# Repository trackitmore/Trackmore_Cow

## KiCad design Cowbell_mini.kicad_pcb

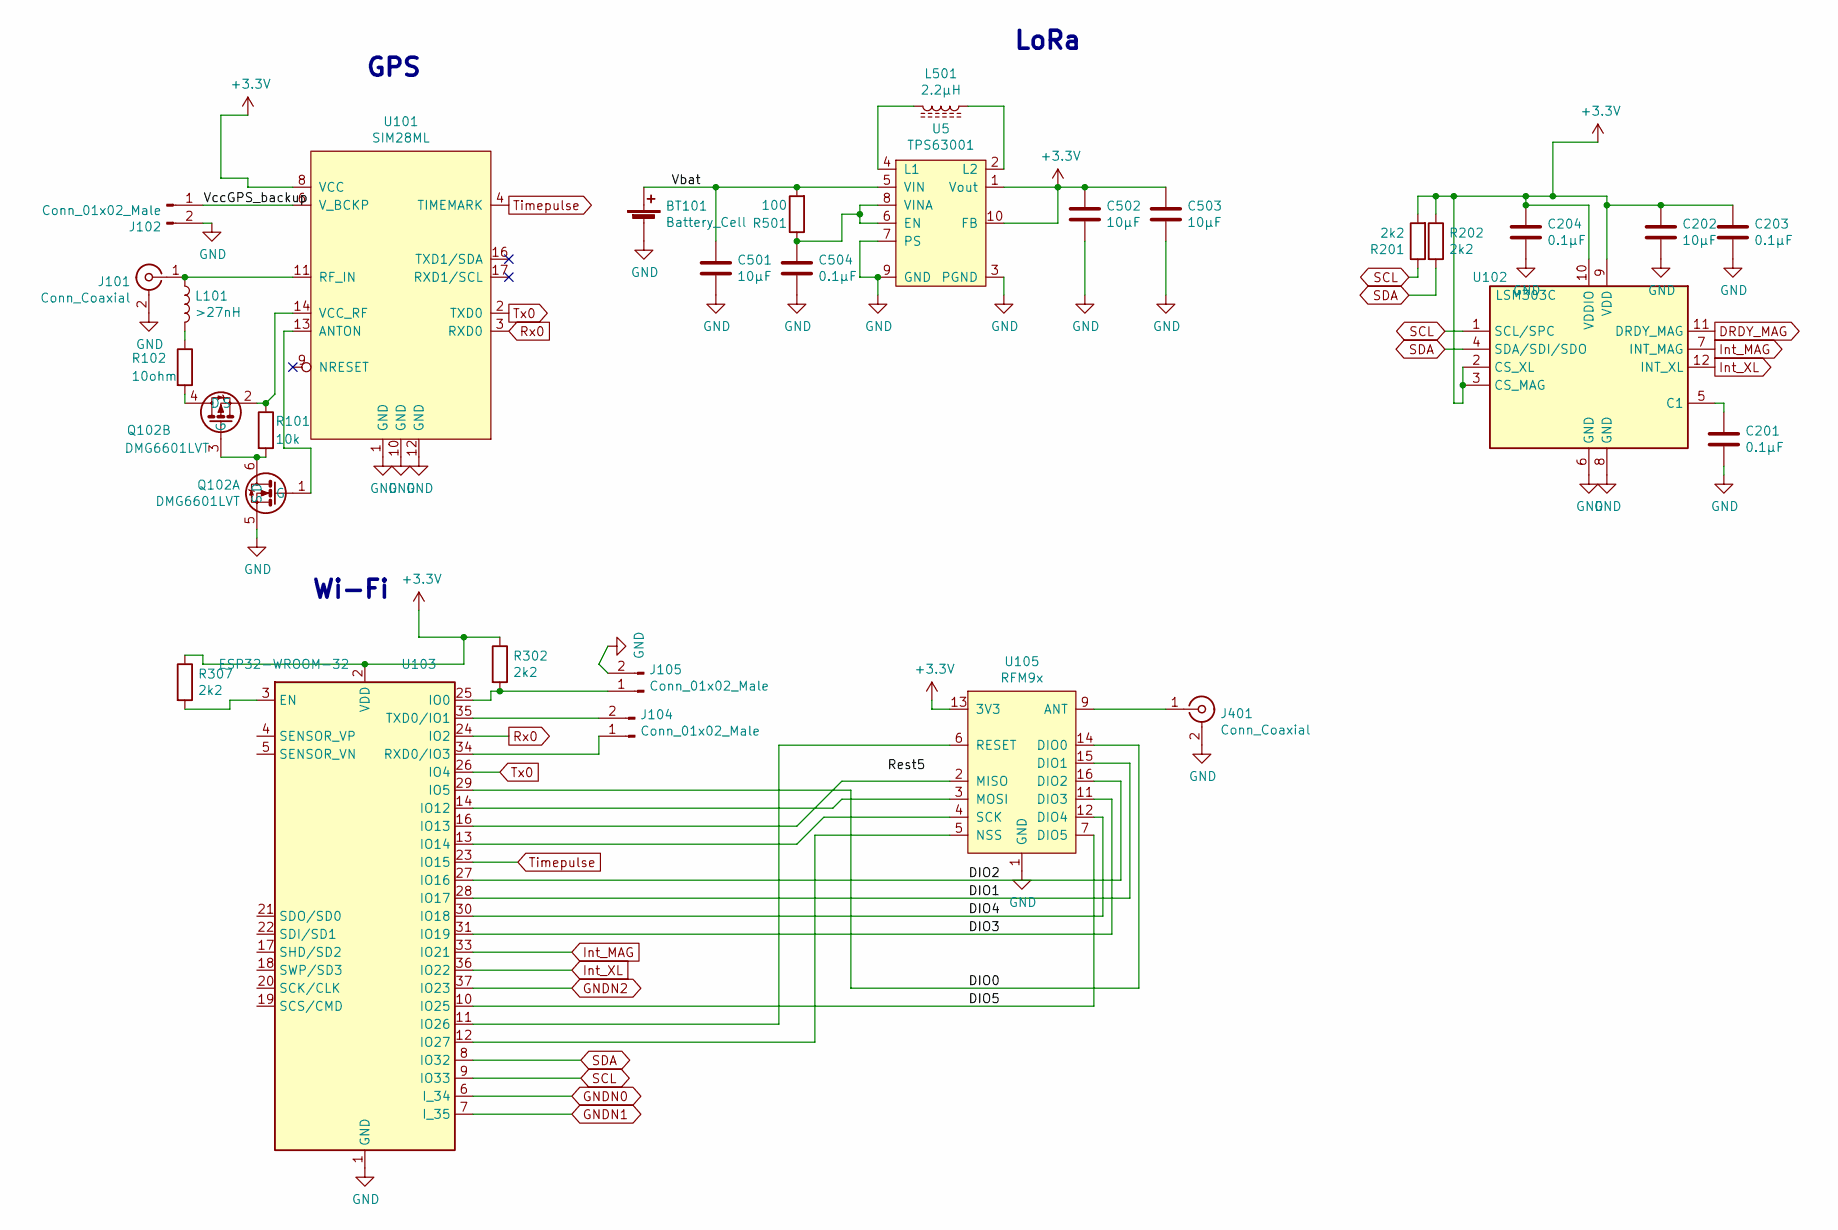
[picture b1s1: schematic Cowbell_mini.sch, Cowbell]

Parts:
BT101: Battery_Cell; batt_Connector
C201, C203, C204, C504: 0.1µF; C_0603_1608Metric
C202, C501, C502, C503: 10µF; C_0603_1608Metric
J101, J401: Conn_Coaxial; u.fl
J102, J104, J105: Conn_01x02_Male; Pin_Header_Straight_1x02_Pitch2.54mm
L101: >27nH; L_0402_1005Metric
L501: 2.2µH; NR3015
Q102: DMG6601LVT
R101: 10k; R_0603_1608Metric_Pad1.05x0.95mm_HandSolder
R102: 10ohm; R_0603_1608Metric_Pad1.05x0.95mm_HandSolder
R201, R202, R302, R307: 2k2; R_0603_1608Metric
R501: 100; R_0603_1608Metric_Pad1.05x0.95mm_HandSolder
U5: TPS63001; DRC0010J
U101: SIM28ML
U102: LSM303C; QFN-12_2x2_lsm303c
U103: ESP32-WROOM-32; ESP32-WROOM-32U
U105: RFM9x; RFM95

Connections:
+3V3: C202.1, C203.1, C204.1, C502.1, C503.1, R201.2, R202.1, R302.1, R307.1, U5.1 (Vout), U5.10 (FB), U101.8 (VCC), U102.2 (CS_XL), U102.3 (CS_MAG), U102.9 (VDD), U102.10 (VDDIO), U103.2 (VDD), U105.13 (3V3)
/DIO0: U103.29 (IO5), U105.14 (DIO0)
/DIO1: U103.28 (IO17), U105.15 (DIO1)
/DIO2: U103.27 (IO16), U105.16 (DIO2)
/DIO3: U103.31 (IO19), U105.11 (DIO3)
/DIO4: U103.30 (IO18), U105.12 (DIO4)
/DIO5: U103.10 (IO25), U105.7 (DIO5)
/Vbat: BT101.1 (+), C501.1, R501.2, U5.5 (VIN)
/VccGPS_backup: J102.1, U101.6 (V_BCKP)
DRDY_MAG: U102.11 (DRDY_MAG)
GND: BT101.2 (-), C201.2, C202.2, C203.2, C204.2, C501.2, C502.2, C503.2, C504.2, J101.2 (Ext), J102.2, J105.2, J401.2 (Ext), Q102.5 (S), U5.3 (PGND), U5.7 (PS), U5.9 (GND), U5.11 (PGND), U101.1 (GND), U101.10 (GND), U101.12 (GND), U102.6 (GND), U102.8 (GND), U103.1 (GND), U103.15 (GND), U103.38 (GND), U103.39 (GND), U105.1 (GND), U105.8 (GND), U105.10 (GND)
GNDN0: U103.6 (I_34)
GNDN1: U103.7 (I_35)
GNDN2: U103.37 (IO23)
Int_MAG: U102.7 (INT_MAG), U103.33 (IO21)
Int_XL: U102.12 (INT_XL), U103.36 (IO22)
unnamed: C201.1, U102.5 (C1)
unnamed: C504.1, R501.1, U5.6 (EN), U5.8 (VINA)
unnamed: J101.1 (In), L101.1, U101.11 (RF_IN)
unnamed: J104.1, U103.34 (RXD0/IO3)
unnamed: J104.2, U103.35 (TXD0/IO1)
unnamed: J105.1, R302.2, U103.25 (IO0)
unnamed: J401.1 (In), U105.9 (ANT)
unnamed: L101.2, R102.1
unnamed: L501.1, U5.2 (L2)
unnamed: L501.2, U5.4 (L1)
unnamed: Q102.1 (G), U101.13 (ANTON)
unnamed: Q102.2 (S), R101.1, U101.14 (VCC_RF)
unnamed: Q102.3 (G), Q102.6 (D), R101.2
unnamed: Q102.4 (D), R102.2
unnamed: R307.2, U103.3 (EN)
unnamed: U103.11 (IO26), U105.6 (RESET)
unnamed: U103.12 (IO27), U105.5 (NSS)
unnamed: U103.13 (IO14), U105.4 (SCK)
unnamed: U103.14 (IO12), U105.3 (MOSI)
unnamed: U103.16 (IO13), U105.2 (MISO)
Rx0: U101.3 (RXD0), U103.24 (IO2)
SCL: R201.1, U102.1 (SCL/SPC), U103.9 (IO33)
SDA: R202.2, U102.4 (SDA/SDI/SDO), U103.8 (IO32)
Timepulse: U101.4 (TIMEMARK), U103.23 (IO15)
Tx0: U101.2 (TXD0), U103.26 (IO4)

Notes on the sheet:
GPS
Wi-Fi
LoRa

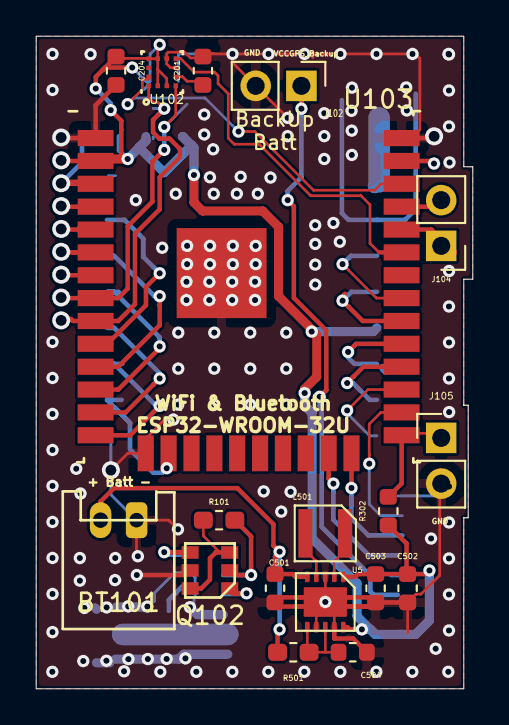
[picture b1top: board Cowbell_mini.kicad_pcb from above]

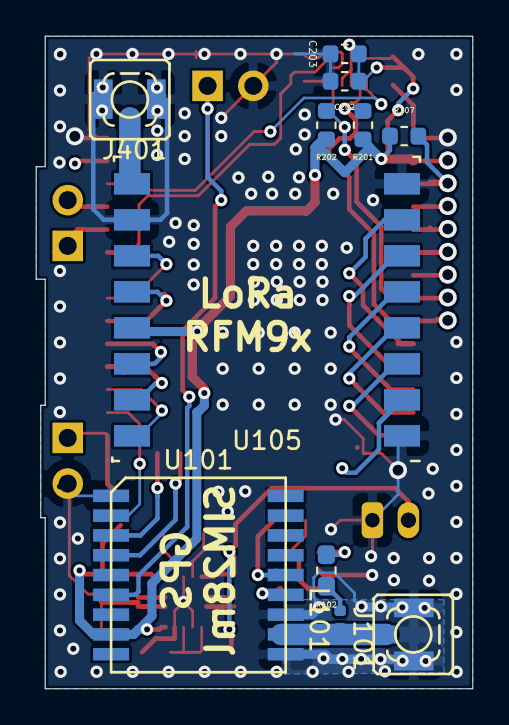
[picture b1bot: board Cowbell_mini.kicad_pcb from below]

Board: 2 copper layers, 24.2 x 36.2 mm, 29 parts (11 on the bottom side), 37 nets.

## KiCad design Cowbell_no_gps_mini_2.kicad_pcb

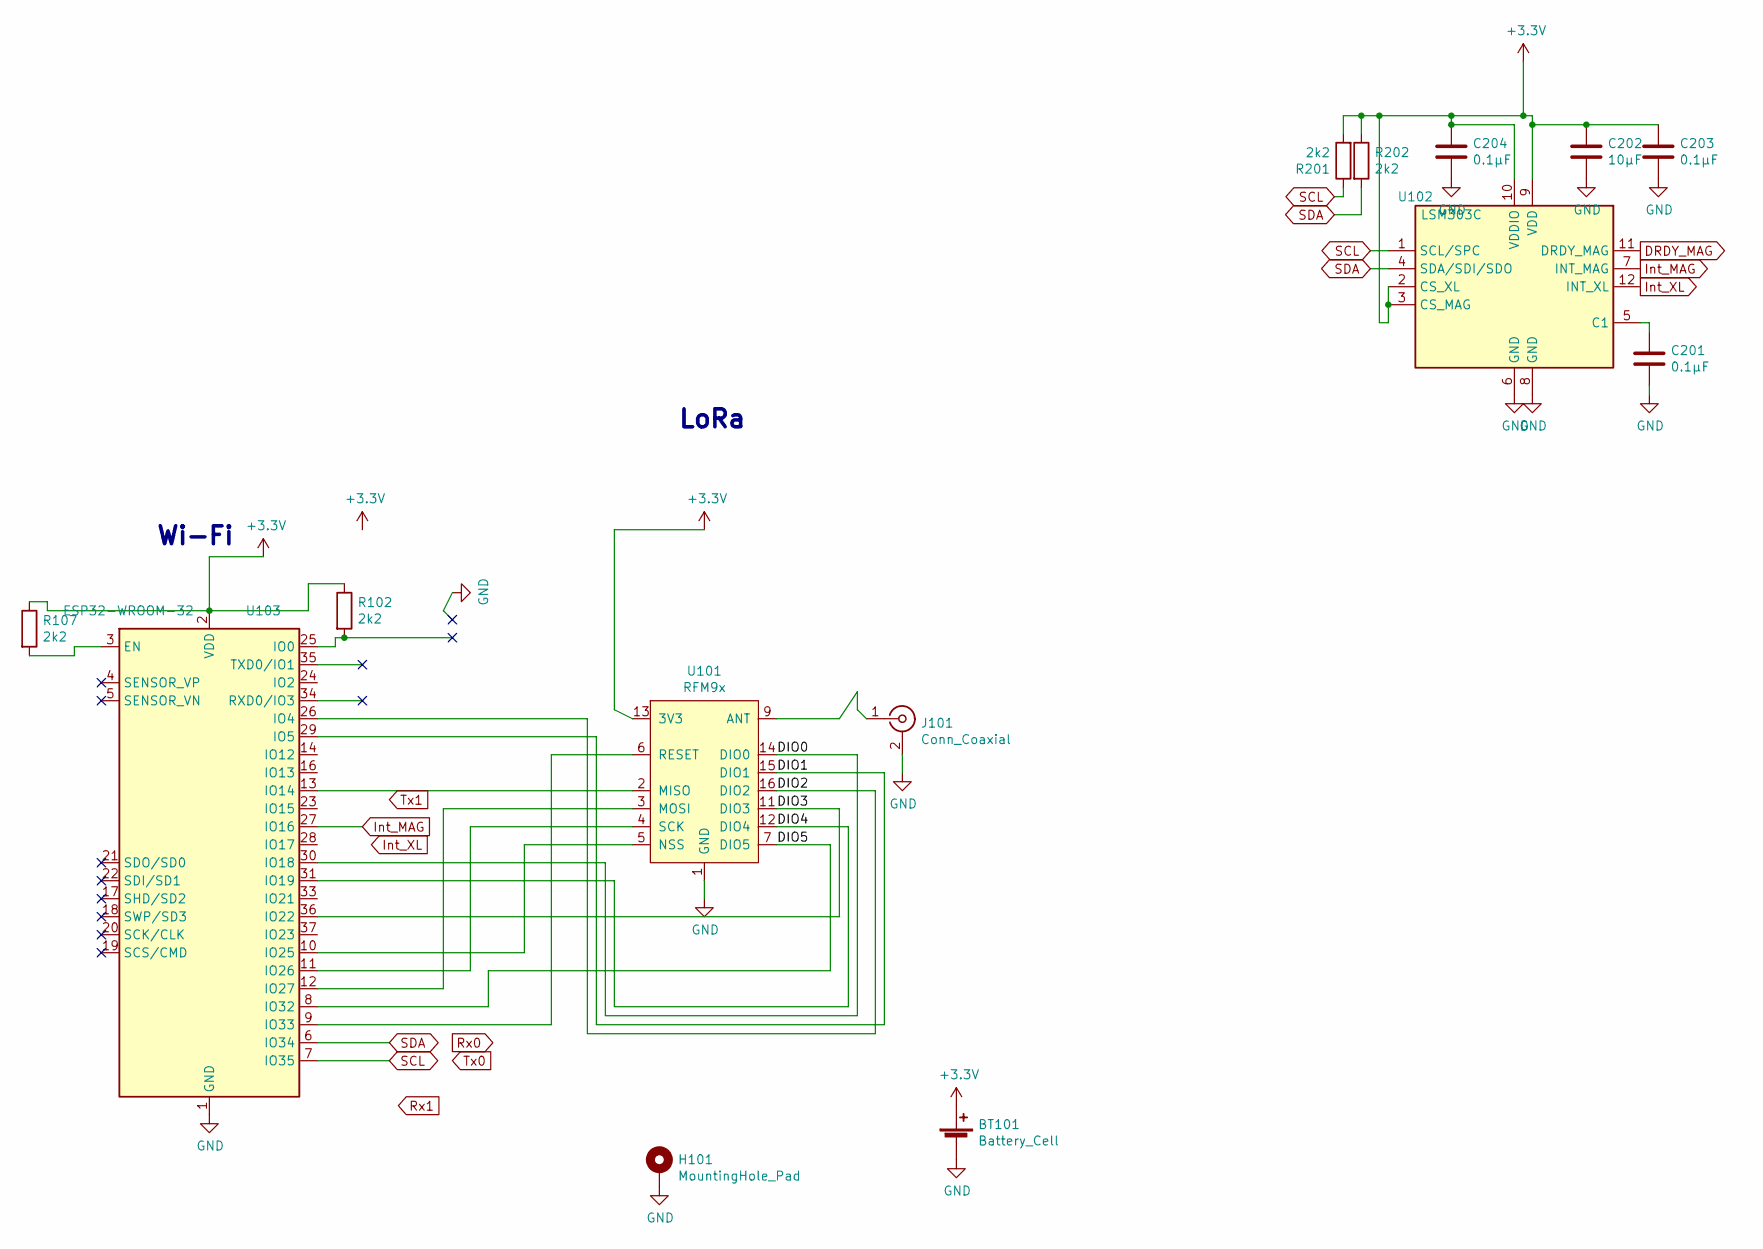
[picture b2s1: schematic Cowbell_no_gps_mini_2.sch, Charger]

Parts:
BT101: Battery_Cell; batt_Connector
C201, C203, C204: 0.1µF; C_0603_1608Metric
C202: 10µF; C_0603_1608Metric
H101: MountingHole_Pad; MountingHole_2.2mm_M2_Pad
J101: Conn_Coaxial; SMA_Molex_73251-1153_EdgeMount_Horizontal
R102, R107, R201, R202: 2k2; R_0603_1608Metric
U101: RFM9x; RFM95
U102: LSM303C; QFN-12_2x2_lsm303c
U103: ESP32-WROOM-32; SP32-WROOM-32U

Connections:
+3V3: BT101.1 (+), C202.1, C203.1, C204.1, R102.1, R107.1, R201.2, R202.1, U101.13 (3V3), U102.2 (CS_XL), U102.3 (CS_MAG), U102.9 (VDD), U102.10 (VDDIO), U103.2 (VDD)
/DIO0: U101.14 (DIO0), U103.30 (IO18)
/DIO1: U101.15 (DIO1), U103.29 (IO5)
/DIO2: U101.16 (DIO2), U103.26 (IO4)
/DIO3: U101.11 (DIO3), U103.36 (IO22)
/DIO4: U101.12 (DIO4), U103.31 (IO19)
/DIO5: U101.7 (DIO5), U103.8 (IO32)
DRDY_MAG: U102.11 (DRDY_MAG)
GND: BT101.2 (-), C201.2, C202.2, C203.2, C204.2, H101.1, J101.2 (Ext), U101.1 (GND), U101.8 (GND), U101.10 (GND), U102.6 (GND), U102.8 (GND), U103.1 (GND), U103.15 (GND), U103.38 (GND), U103.39 (GND)
Int_MAG: U102.7 (INT_MAG), U103.27 (IO16)
Int_XL: U102.12 (INT_XL)
unnamed: C201.1, U102.5 (C1)
unnamed: J101.1 (In), U101.9 (ANT)
unnamed: R102.2, U103.25 (IO0)
unnamed: R107.2, U103.3 (EN)
unnamed: U101.2 (MISO), U103.13 (IO14)
unnamed: U101.3 (MOSI), U103.12 (IO27)
unnamed: U101.4 (SCK), U103.11 (IO26)
unnamed: U101.5 (NSS), U103.10 (IO25)
unnamed: U101.6 (RESET), U103.9 (IO33)
SCL: R201.1, U102.1 (SCL/SPC), U103.7 (IO35)
SDA: R202.2, U102.4 (SDA/SDI/SDO), U103.6 (IO34)

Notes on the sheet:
Wi-Fi
LoRa

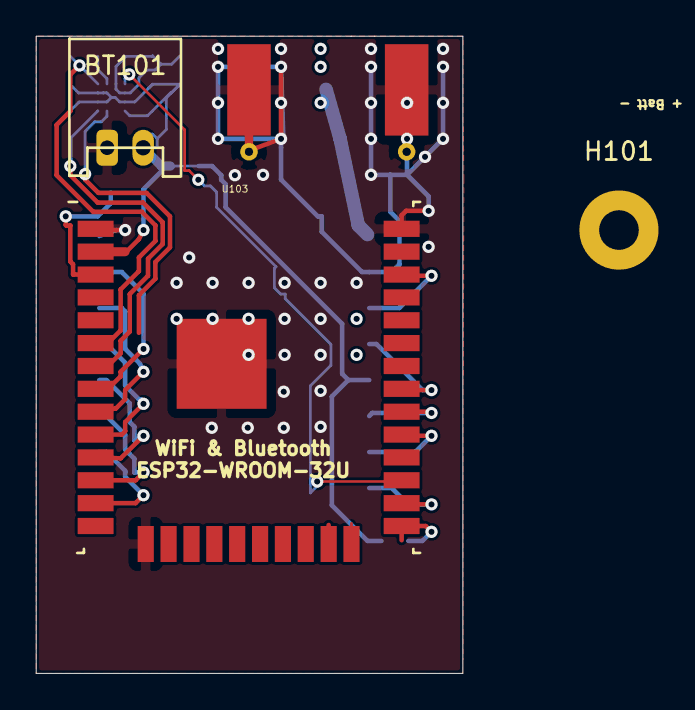
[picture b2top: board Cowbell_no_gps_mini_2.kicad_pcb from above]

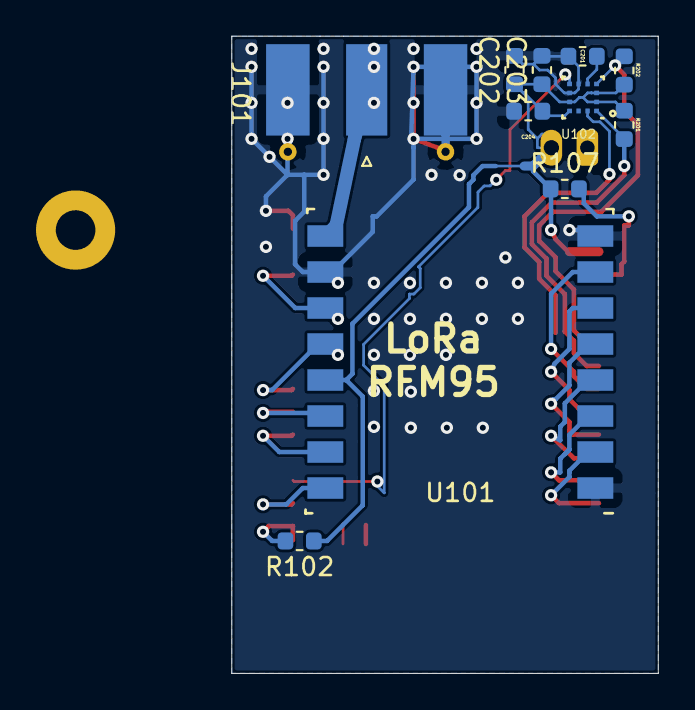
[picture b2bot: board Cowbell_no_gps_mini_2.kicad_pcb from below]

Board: 2 copper layers, 23.7 x 35.4 mm, 14 parts (11 on the bottom side), 20 nets.

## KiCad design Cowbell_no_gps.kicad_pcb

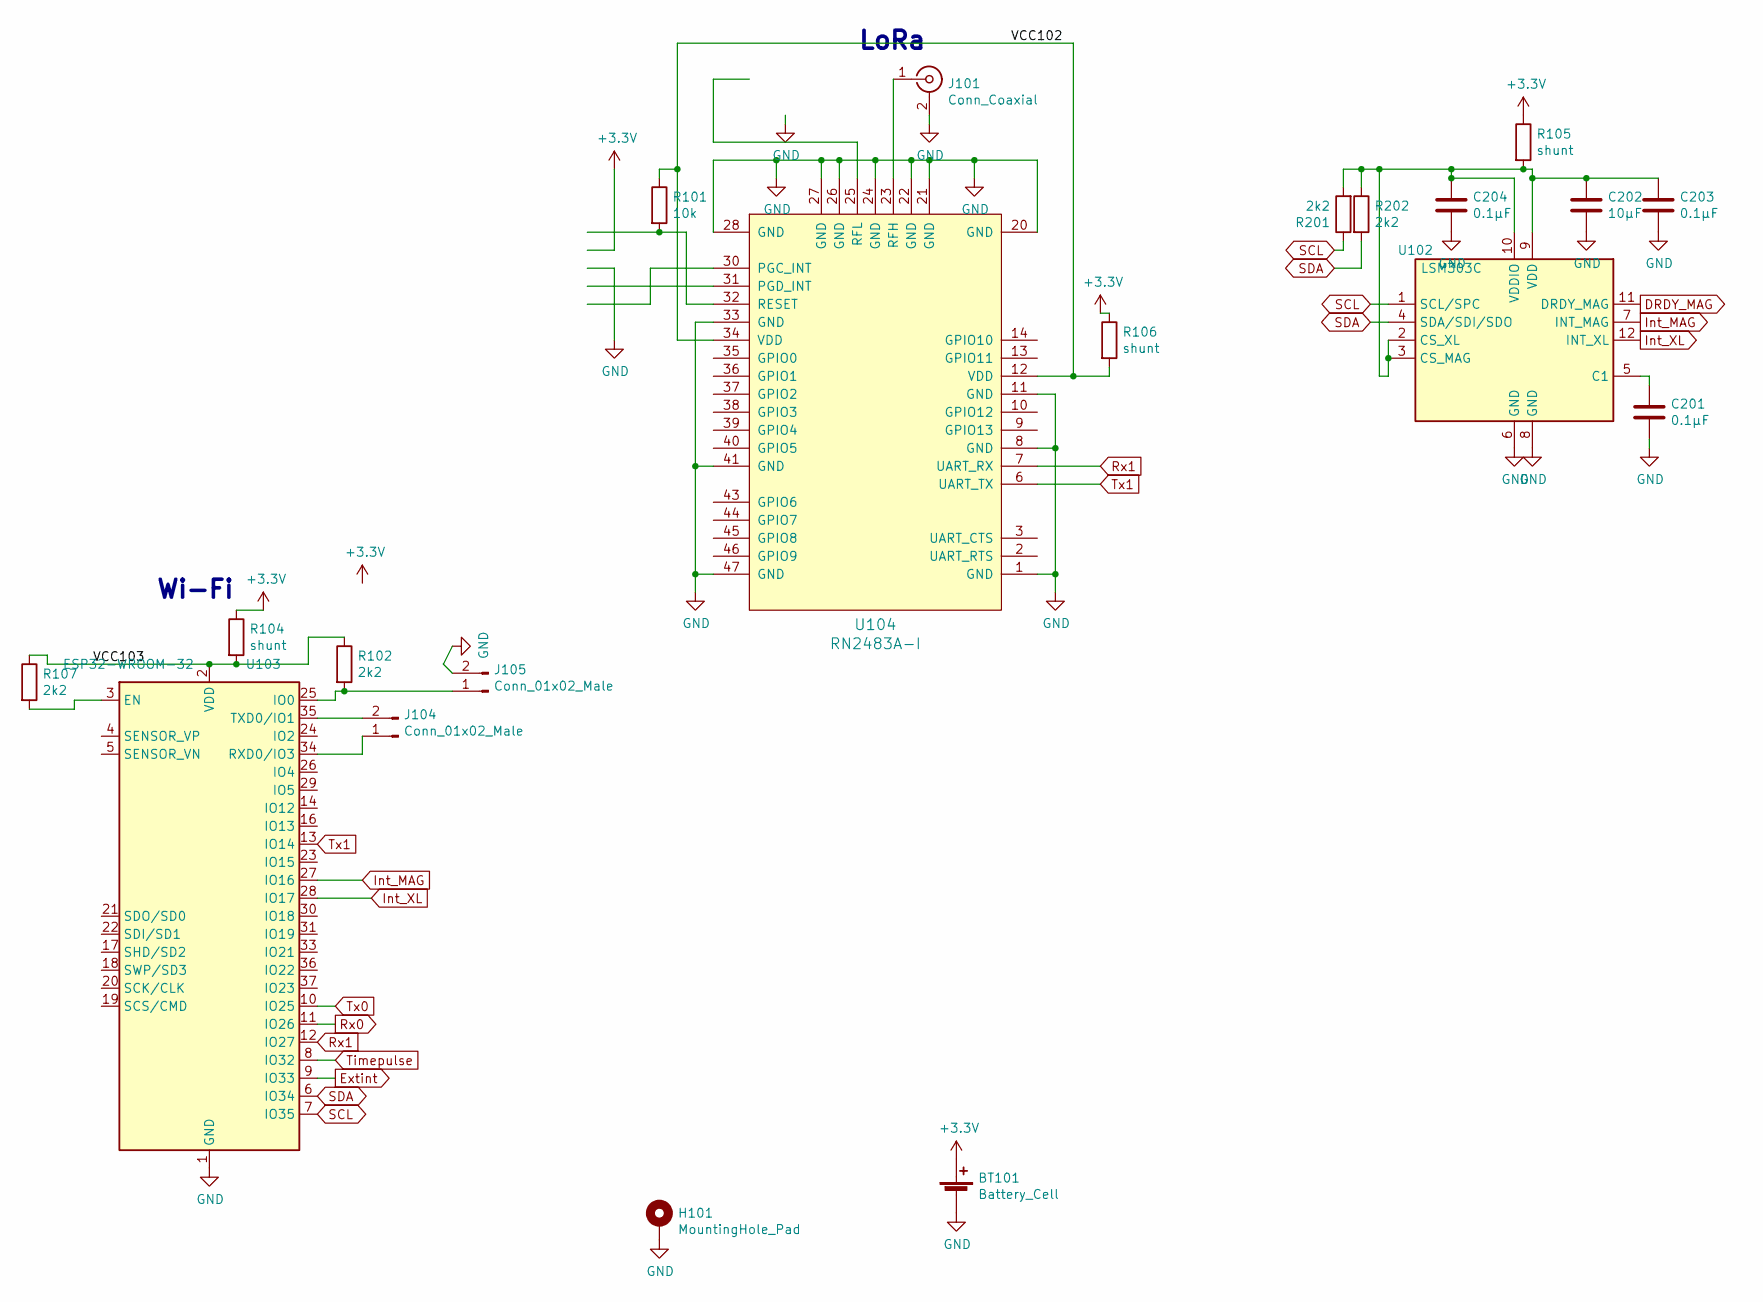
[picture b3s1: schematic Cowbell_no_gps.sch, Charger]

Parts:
BT101: Battery_Cell; batt_Connector
C201, C203, C204: 0.1µF; C_0603
C202: 10µF; C_0603_HandSoldering
H101: MountingHole_Pad; MountingHole_2.2mm_M2_Pad
J101: Conn_Coaxial; Molex_SMA_Jack_Edge_Mount
J104, J105: Conn_01x02_Male; Pin_Header_Straight_1x02_Pitch2.54mm
R101: 10k; R_0603_HandSoldering
R102, R107, R201, R202: 2k2; R_0603
R104, R105, R106: shunt; R_0603
U102: LSM303C; QFN-12_2x2_lsm303c
U103: ESP32-WROOM-32; SP32-WROOM-32U
U104: RN2483A-I; RN2483; Mouser_PN 579-RN2483A-I/RM104

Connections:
+3V3: BT101.1 (+), R104.1, R105.1, R106.1
/VCC102: R101.1, R106.2, U104.12 (VDD), U104.34 (VDD)
/VCC103: R102.1, R104.2, R107.1, U103.2 (VDD)
DRDY_MAG: U102.11 (DRDY_MAG)
Extint: U103.9 (IO33)
GND: BT101.2 (-), C201.2, C202.2, C203.2, C204.2, H101.1, J101.2 (Ext), J105.2, U102.6 (GND), U102.8 (GND), U103.1 (GND), U103.15 (GND), U103.38 (GND), U103.39 (GND), U104.1 (GND), U104.8 (GND), U104.11 (GND), U104.20 (GND), U104.21 (GND), U104.22 (GND), U104.24 (GND), U104.26 (GND), U104.27 (GND), U104.28 (GND), U104.33 (GND), U104.41 (GND), U104.47 (GND)
Int_MAG: U102.7 (INT_MAG), U103.27 (IO16)
Int_XL: U102.12 (INT_XL), U103.28 (IO17)
unnamed: C201.1, U102.5 (C1)
unnamed: C202.1, C203.1, C204.1, R105.2, R201.2, R202.1, U102.2 (CS_XL), U102.3 (CS_MAG), U102.9 (VDD), U102.10 (VDDIO)
unnamed: J101.1 (In), U104.23 (RFH)
unnamed: J104.1, U103.34 (RXD0/IO3)
unnamed: J104.2, U103.35 (TXD0/IO1)
unnamed: J105.1, R102.2, U103.25 (IO0)
unnamed: R101.2, U104.32 (RESET)
unnamed: R107.2, U103.3 (EN)
Rx0: U103.11 (IO26)
Rx1: U103.12 (IO27), U104.7 (UART_RX)
SCL: R201.1, U102.1 (SCL/SPC), U103.7 (IO35)
SDA: R202.2, U102.4 (SDA/SDI/SDO), U103.6 (IO34)
Timepulse: U103.8 (IO32)
Tx0: U103.10 (IO25)
Tx1: U103.13 (IO14), U104.6 (UART_TX)

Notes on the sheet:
Wi-Fi
LoRa

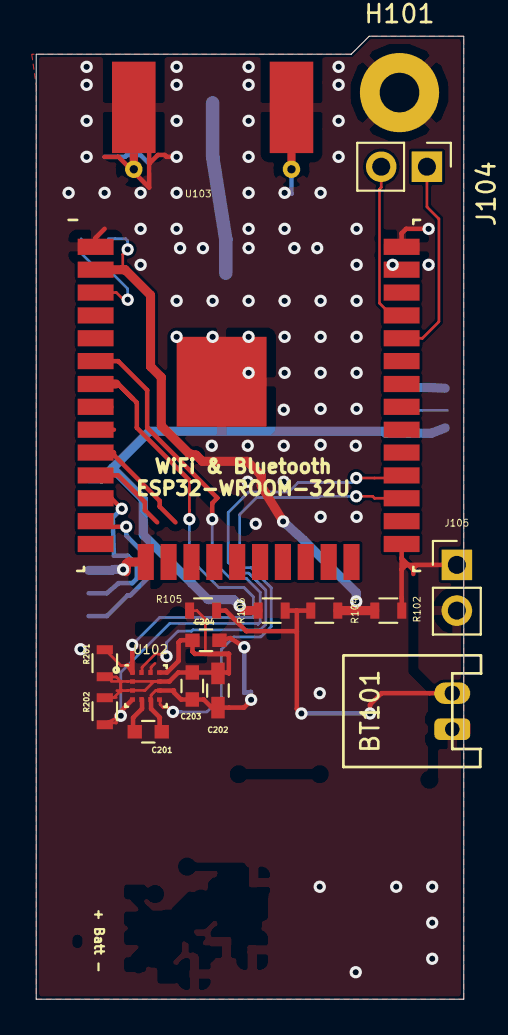
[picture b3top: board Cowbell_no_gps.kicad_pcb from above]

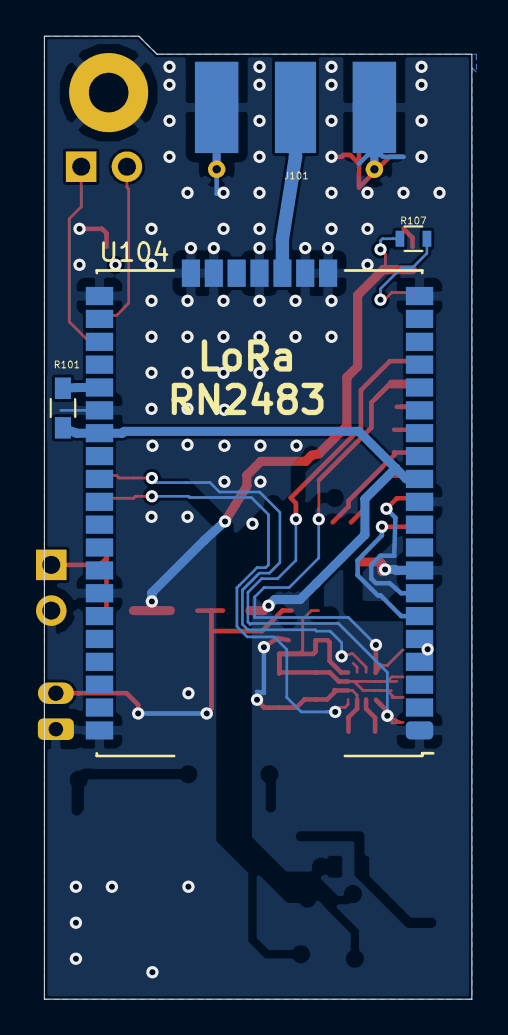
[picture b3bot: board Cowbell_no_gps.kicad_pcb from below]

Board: 2 copper layers, 23.7 x 53.5 mm, 20 parts (4 on the bottom side), 18 nets.

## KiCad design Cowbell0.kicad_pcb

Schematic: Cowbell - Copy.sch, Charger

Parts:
C1: 1nF; C_0603_HandSoldering
C2: 330pF; C_0603_HandSoldering
C3: C; C_0603_HandSoldering
C4: 0.1F; CP_Radial_D13.0mm_P5.00mm
C201, C203, C204: 0.1µF; C_0603
C202: 10µF; C_0603_HandSoldering
J1: Conn_Coaxial; u.fl
J10: V_BCKP; Pin_d0.9mm_L10.0mm_W2.4mm_FlatFork
J11: GND; Pin_d0.9mm_L10.0mm_W2.4mm_FlatFork
J101, J102: Conn_Coaxial; Molex_SMA_Jack_Edge_Mount
J103: Conn_01x06_Male; Pin_Header_Straight_1x06_Pitch2.54mm
J104, J105: Conn_01x02_Male; Pin_Header_Straight_1x02_Pitch2.54mm
L1: L_Core_Ferrite_Coupled; WE-EHPI 6x6
R1: DNC; R_0603_HandSoldering
R101: 10k; R_0603_HandSoldering
R201, R202: 2k2; R_0603
TP1, TP2, TP3, TP4, TP5, TP6: TestPoint; Pin_d0.9mm_L10.0mm_W2.4mm_FlatFork
TP_Vaux1: TestPoint; Pin_d0.9mm_L10.0mm_W2.4mm_FlatFork
TP_Vstor1: TestPoint; Pin_d0.9mm_L10.0mm_W2.4mm_FlatFork
U1: LTC3108; LTC3108_SSOP-16
U101: NEO-M8
U102: LSM303C; QFN-12_2x2_lsm303c
U103: ESP32-WROOM-32; SP32-WROOM-32U
U104: RN2483A-I; RN2483; Mouser_PN 579-RN2483A-I/RM104

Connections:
DRDY_MAG: U102.11 (DRDY_MAG)
Extint: U101.4 (EXTINT), U103.9 (IO33)
GND: C3.2, C4.2, C201.2, C202.2, C203.2, C204.2, J1.2 (Ext), J11.1, J101.2 (Ext), J102.2 (Ext), J103.3, J105.2, L1.4, U1.1, U1.8, U1.9, U1.10, U1.16, U101.10 (GND), U101.12 (GND), U101.13 (GND), U101.24 (GND), U102.6 (GND), U102.8 (GND), U103.1 (GND), U103.15 (GND), U103.38 (GND), U103.39 (GND), U104.1 (GND), U104.8 (GND), U104.11 (GND), U104.20 (GND), U104.21 (GND), U104.22 (GND), U104.24 (GND), U104.26 (GND), U104.27 (GND), U104.28 (GND), U104.33 (GND), U104.41 (GND), U104.47 (GND)
Int_MAG: U102.7 (INT_MAG)
Int_XL: U102.12 (INT_XL)
unnamed: C1.1, U1.13
unnamed: C1.2, C2.2, L1.3
unnamed: C2.1, U1.14
unnamed: C3.1, TP_Vaux1.1, U1.2, U1.11
unnamed: C4.1, TP_Vstor1.1, U1.3
unnamed: C201.1, U102.5 (C1)
unnamed: J1.1 (In), U101.11 (RF_IN)
unnamed: J10.1, U101.22 (V_BCKP)
unnamed: J101.1 (In), U104.23 (RFH)
unnamed: J102.1 (In), U104.25 (RFL)
unnamed: J103.1, R101.2, U104.32 (RESET)
unnamed: J103.4, U104.31 (PGD_INT)
unnamed: J103.5, U104.30 (PGC_INT)
unnamed: L1.1, TP1.1
unnamed: L1.2, U1.15
unnamed: R1.1, U101.9 (VCC_RF)
unnamed: R1.2, U101.8 (RESET_N)
unnamed: TP2.1, U1.5
unnamed: TP3.1, U1.7
unnamed: TP4.1, U1.6
unnamed: TP5.1, U1.12
unnamed: TP6.1, U1.4
unnamed: J105.1, U103.25 (IO0)
unnamed: J104.1, U103.34 (RXD0/IO3)
unnamed: J104.2, U103.35 (TXD0/IO1)
Rx0: U101.21 (RXD), U103.11 (IO26)
Rx1: U103.12 (IO27), U104.7 (UART_RX)
SCL: R201.1, U102.1 (SCL/SPC), U103.7 (IO35)
SDA: R202.2, U102.4 (SDA/SDI/SDO), U103.6 (IO34)
Timepulse: U101.3 (TIMEPULS), U103.8 (IO32)
Tx0: U101.20 (TXD), U103.10 (IO25)
Tx1: U103.13 (IO14), U104.6 (UART_TX)

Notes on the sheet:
GPS
Wi-Fi
LoRa

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
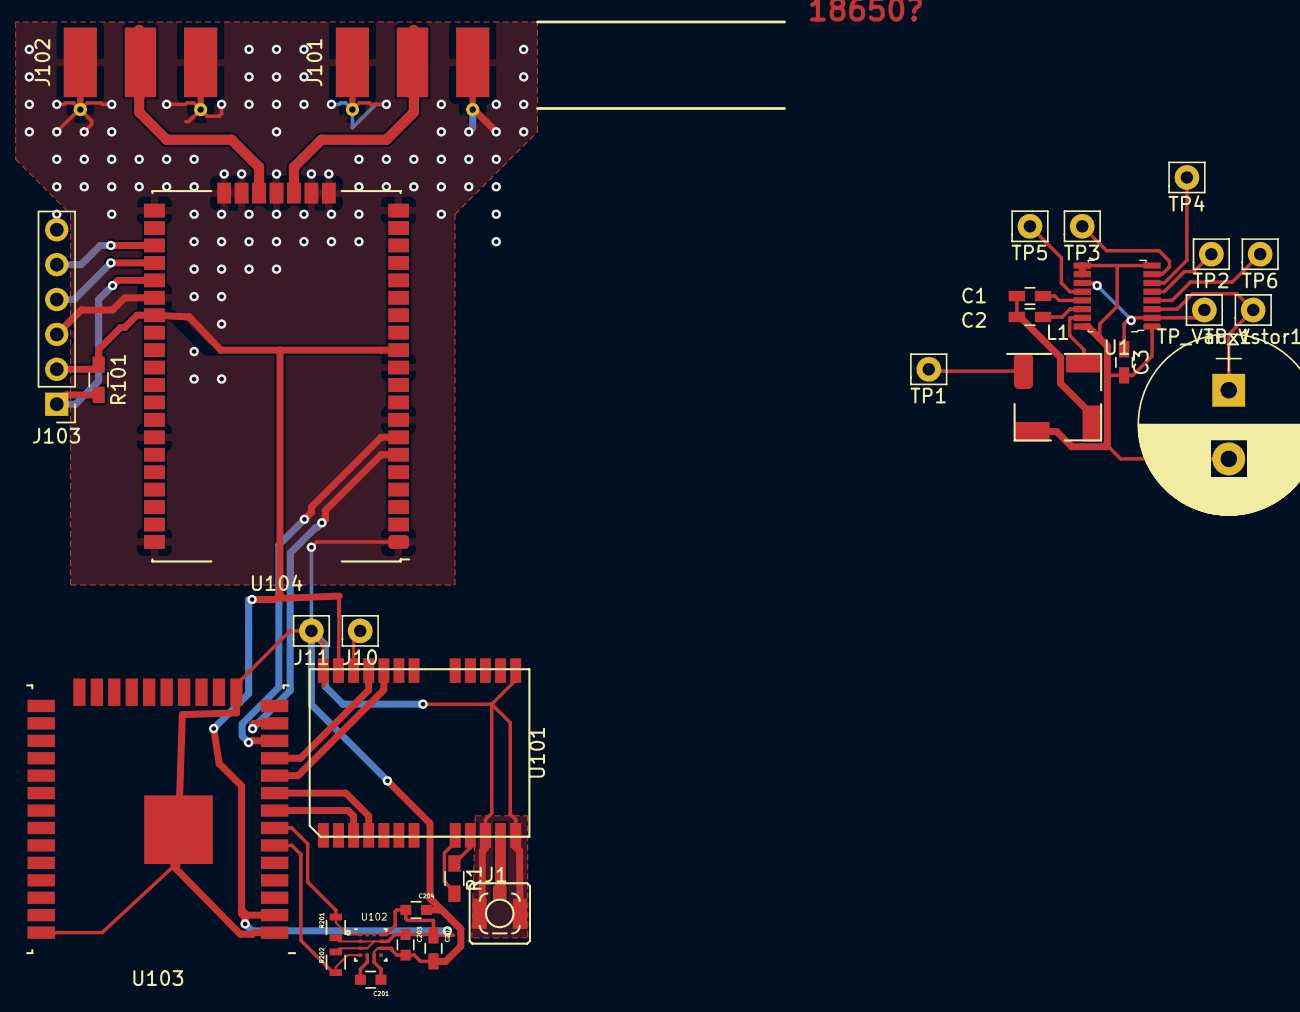
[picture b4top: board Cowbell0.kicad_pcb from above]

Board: 2 copper layers, 32 parts (0 on the bottom side), 32 nets.

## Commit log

2019-03-12 Finished design
2019-04-02 Revert "Delete Emborg.bck"
    This reverts commit 09d27a02d29fe968c1b7a81d1ac8e51f44b27ffa.
2019-04-02 Revert "Delete Emborg.dcm"
    This reverts commit c4a0c2c87ce3134f79510e9a5a0e6fc7b62b94bc.
2019-04-02 Revert "Delete Emborg.lib"
    This reverts commit cf9496bd58ba884746e156cb7f657ddb5a494be7.
2019-04-02 Revert "Delete sym-lib-table"
    This reverts commit 0304bca046c8f614dbed9e12e921aacf97358f74.
2019-04-02 Revert "Delete thinkerbell.kicad_pcb-bak"
    This reverts commit 65bb71eede209ff8c9db95584b85d2a653b0d64a.
2019-04-02 Revert "Delete thinkerbell.pro"
    This reverts commit 58df75db17a912b9343e4aff8fe34464ce08963a.
2019-04-02 Revert "Delete Cowbell1.kicad_pcb"
    This reverts commit d80b693f933305171241f23dd8f8959974bb5168.
2019-04-02 Revert "Delete Cowbell0.kicad_pcb"
    This reverts commit 252e33d99e0bc0e285b6e3a8f17d518fcc3dd87e.
2019-04-02 Revert "Delete Cowbell.sch"
    This reverts commit 978fadb779a8fa3cc5b9792794aa4cbf9cfdb8ff.
2019-04-02 Revert "Delete Cowbell.xml"
    This reverts commit 881aa0ef93652d590a35256fd297fa05b056862a.
2019-04-02 Revert "Delete Cowbell.pro"
    This reverts commit 091eba08f6241ed96e29c814f36a258aab0e2ca5.
2019-04-02 Revert "Delete Cowbell.net"
    This reverts commit 7cafb855b5cd9209ead3aa4c814db5f94e171ee6.
2019-04-02 Revert "Delete Cowbell - Copy.sch"
    This reverts commit ae1c11a69f8279535f7880325fb270926ae6e74f.
2019-04-02 Revert "Delete .gitattributes"
    This reverts commit 4acfe99408becdc238a615270ff10b1e2c5de4c9.
2019-04-02 Revert "Delete LTC3108_SSOP-16.kicad_mod"
    This reverts commit f564a00daeaa7909a267ca2040881fb35d2d5901.
2019-04-02 Revert "Delete NEO-M8.kicad_mod"
    This reverts commit 1ef6422d8f3c24d0bca9058cdd3533081b6ed742.
2019-04-02 Revert "Delete QFN-12_2x2_lsm303c.kicad_mod"
    This reverts commit 21fc2b2070f548b9e88a3c2e228f056f9d769ac0.
2019-04-02 Revert "Delete QFP-80_17.78x26.67_Pitch1.27mm.kicad_mod"
    This reverts commit 5e69e16ba0a7954603f7a7df822ec4fd45762fe7.
2019-04-02 Revert "Delete RN2483.kicad_mod"
    This reverts commit e23ea6ab3ff4c29680038cb41fe7873a4a4a5c81.
2019-04-02 Revert "Delete SP32-WROOM-32U.kicad_mod"
    This reverts commit 5fa6db17635eadc840dfb2fc761eeff62a0f5e57.
2019-04-02 Revert "Delete SSOP-16-LTC3108.kicad_mod"
    This reverts commit 1ba041bbb633a4fccae1273e11786fdac62c0148.
2019-04-02 Revert "Delete batt_Connector.kicad_mod"
    This reverts commit 9847d93e790d4d2d9b095128e2b6511a8e429725.
2019-04-02 Revert "Delete WE-EHPI 6x6.kicad_mod"
    This reverts commit 5fb4d74c714d4724239fdc0bf541602c3e96ddf4.
2019-04-02 Revert "Delete u.fl.kicad_mod"
    This reverts commit 5432f16fb51e91493d83f1e084b6664b42315e9d.
2019-04-02 Revert "Delete Cowbell-cache.lib"
    This reverts commit deac368cf7cbae8f2a3d845c4ad8eac762145e6c.
2019-04-02 Revert "Delete Cowbell-rescue.dcm"
    This reverts commit 3877b9671cf0eeddc5ad82af6c877a2a42698372.
2019-04-02 Revert "Delete Cowbell-rescue.lib"
    This reverts commit 5e4fc595a82f6b163571de27dac84ba1a4aeee0b.
2019-04-02 Revert "Delete Cowbell.bak"
    This reverts commit 83bee5dd43be2db377b36096ba5a354214a55166.
2019-04-02 Revert "Delete Cowbell.kicad_pcb"
    This reverts commit 747ba4d31c338c22f969143d4c642bb9dc160634.
2019-04-02 Revert "Delete Cowbell.kicad_pcb-bak"
    This reverts commit a0f5cc8e1a52d7afc8a1a5b4756ecd4a47175799.
2019-04-05 Removed unnissray files
2019-04-05 Added code
2019-04-11 Add files via upload
    skifte til sim28
2019-04-26 Upload
2019-04-26 Revert "Added code"
    This reverts commit 917a6e6e95a4ee82794b217ccadd158d93d931af.
2019-04-26 Revert "Removed unnissray files"
    This reverts commit eb4dde10ade02bed4aa6936b6fc7d44ad99826a2.
2019-04-26 Revert "Upload"
    This reverts commit f814fb6d94db8a858d7b366ca888cf0d9b009713.
2019-05-04 Updated to newest version
2019-05-04 Final version
